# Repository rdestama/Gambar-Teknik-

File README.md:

# Gambar-Teknik-
D. R. N. Nuswantoro, "Gambar Teknik Semester 1 2021," File ini merupakan kumpulan tugas gambar teknik semester 1 tahun 2021 di UNY, Oct 2021.

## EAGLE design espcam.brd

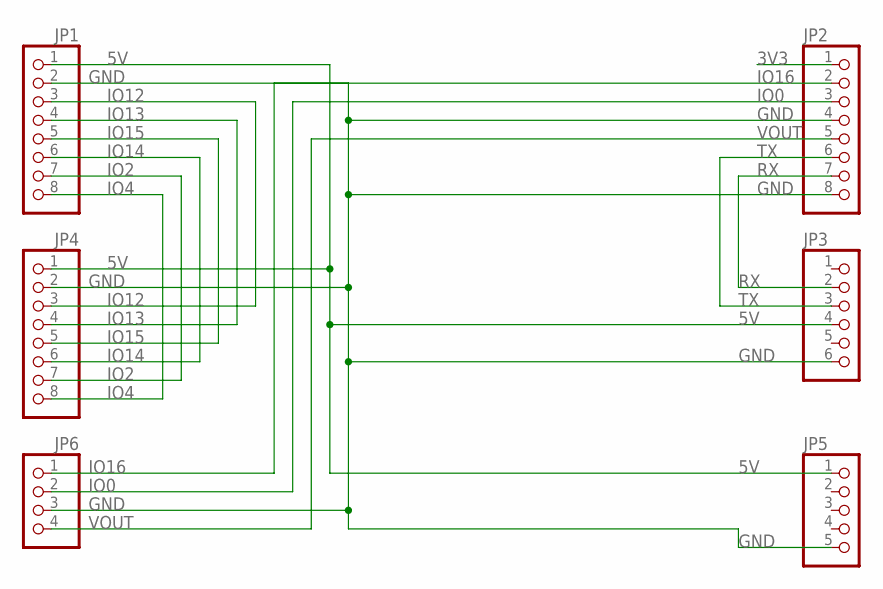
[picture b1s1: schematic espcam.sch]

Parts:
JP1, JP2, JP4: PINHD-1X8; 1X08
JP3: PINHD-1X6; 1X06
JP5: PINHD-1X5; 1X05
JP6: PINHD-1X4; 1X04

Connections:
3V3: JP2.1
5V: JP1.1, JP3.4, JP4.1, JP5.1
GND: JP1.2, JP2.4, JP2.8, JP3.6, JP4.2, JP5.5, JP6.3
IO0: JP2.3, JP6.2
IO2: JP1.7, JP4.7
IO4: JP1.8, JP4.8
IO12: JP1.3, JP4.3
IO13: JP1.4, JP4.4
IO14: JP1.6, JP4.6
IO15: JP1.5, JP4.5
IO16: JP2.2, JP6.1
RX: JP2.7, JP3.2
TX: JP2.6, JP3.3
VOUT: JP2.5, JP6.4

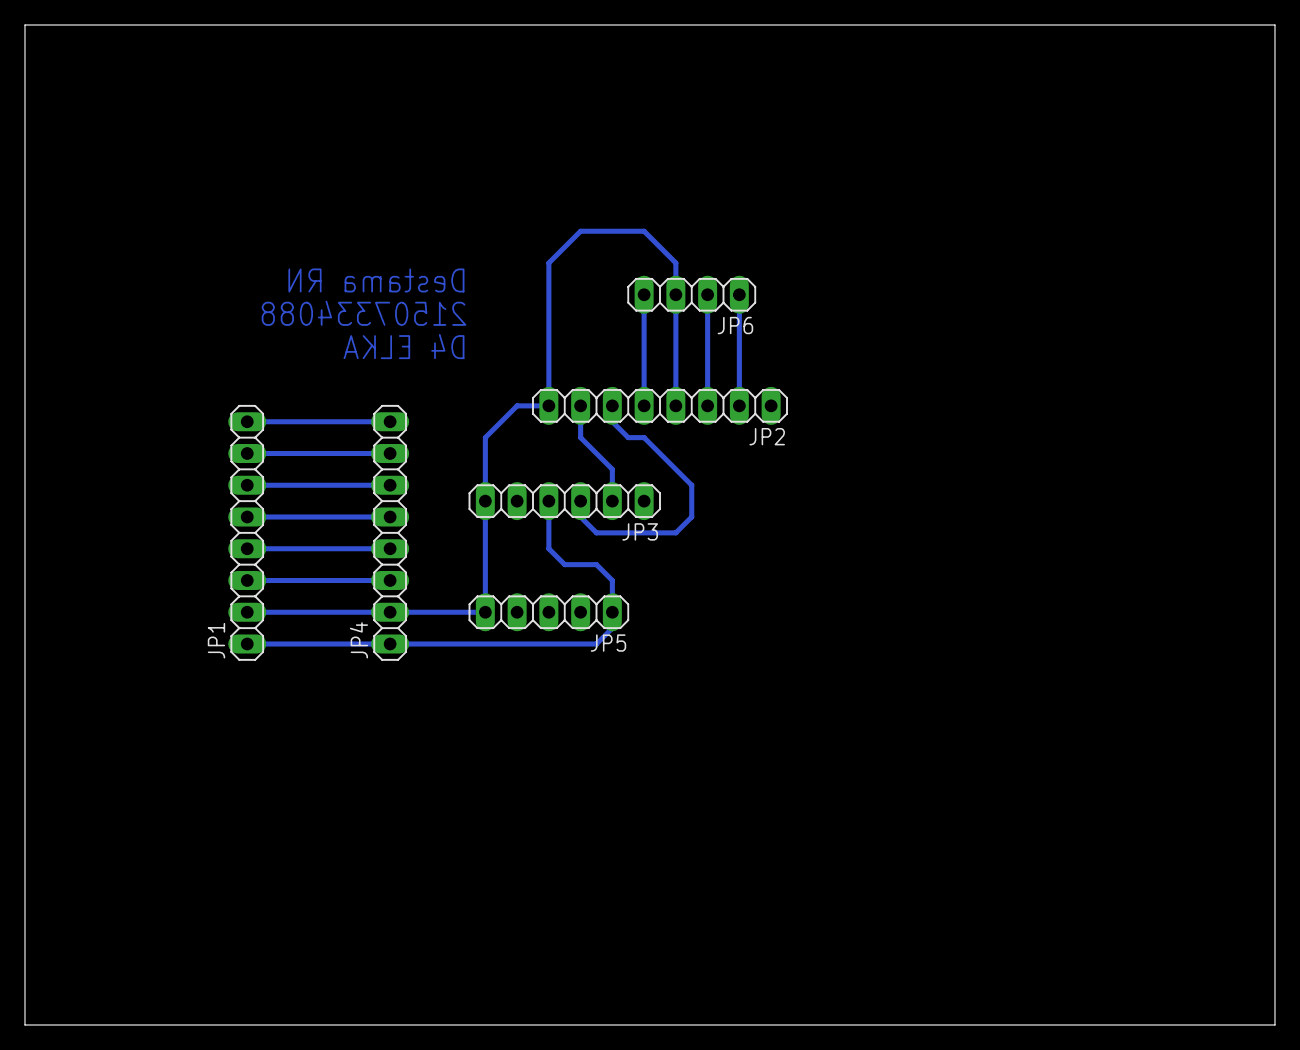
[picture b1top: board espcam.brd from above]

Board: 2 copper layers, 100.0 x 80.0 mm, 6 parts (0 on the bottom side), 13 nets.

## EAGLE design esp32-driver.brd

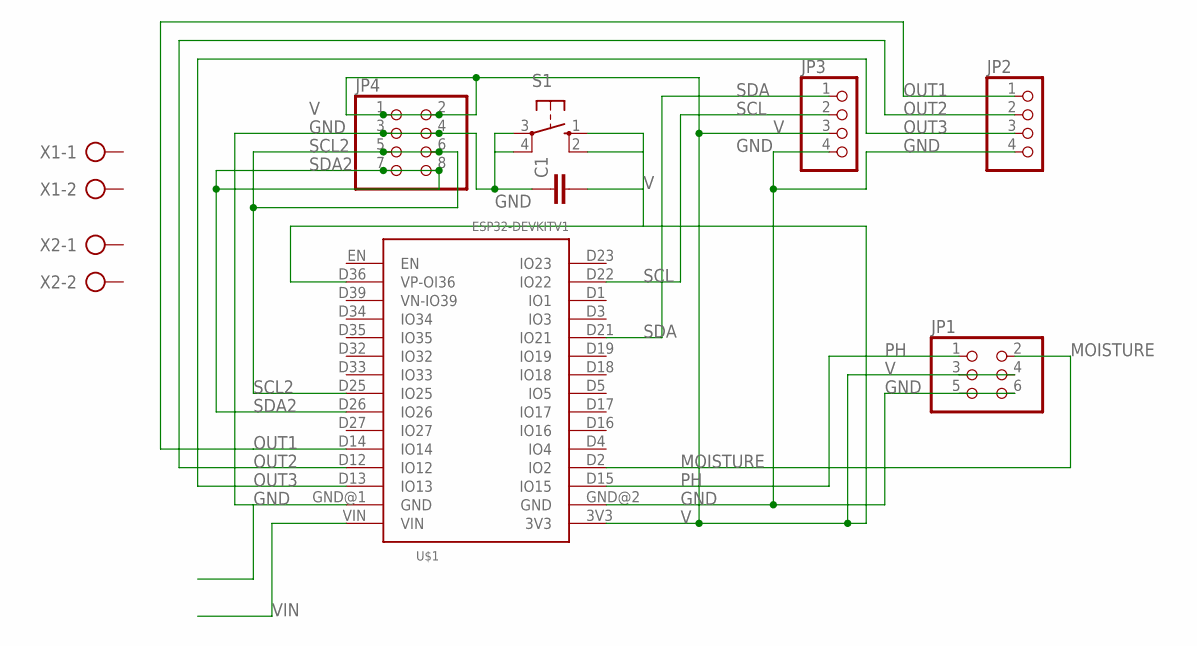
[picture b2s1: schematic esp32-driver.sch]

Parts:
C1: C-EU050-030X075; C050-030X075
JP1: PINHD-2X3; 2X03
JP2, JP3: PINHD-1X4; 1X04
JP4: PINHD-2X4; 2X04
S1: 10-XX; B3F-10XX
U$1: ESP32DEVKITV1; ESP32-DEVKITV1
X1, X2: AK300/2

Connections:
GND: C1.1, JP1.5, JP1.6, JP2.4, JP3.4, JP4.3, JP4.4, S1.3, S1.4 (P1), U$1.GND@1 (GND), U$1.GND@2 (GND)
MOISTURE: JP1.2, U$1.D2 (IO2)
OUT1: JP2.1, U$1.D14 (IO14)
OUT2: JP2.2, U$1.D12 (IO12)
OUT3: JP2.3, U$1.D13 (IO13)
PH: JP1.1, U$1.D15 (IO15)
SCL: JP3.2, U$1.D22 (IO22)
SCL2: JP4.5, JP4.6, U$1.D25 (IO25)
SDA: JP3.1, U$1.D21 (IO21)
SDA2: JP4.7, JP4.8, U$1.D26 (IO26)
V: C1.2, JP1.3, JP1.4, JP3.3, JP4.1, JP4.2, S1.1 (S), S1.2 (S1), U$1.3V3, U$1.D36 (VP-OI36)
VIN: U$1.VIN

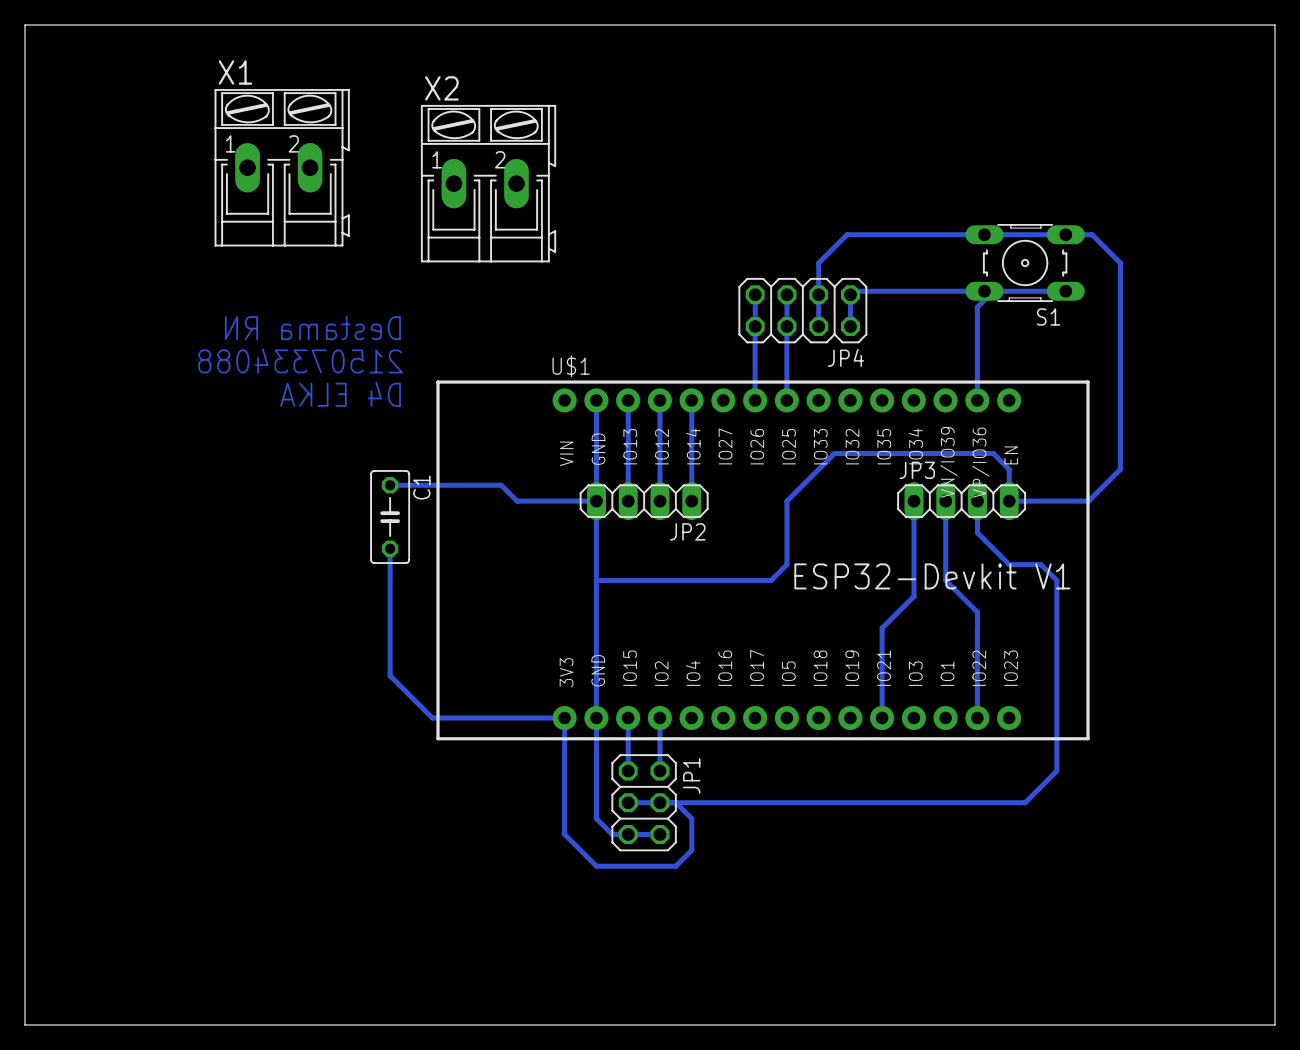
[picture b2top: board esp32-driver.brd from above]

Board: 2 copper layers, 100.0 x 80.0 mm, 9 parts (0 on the bottom side), 11 nets.

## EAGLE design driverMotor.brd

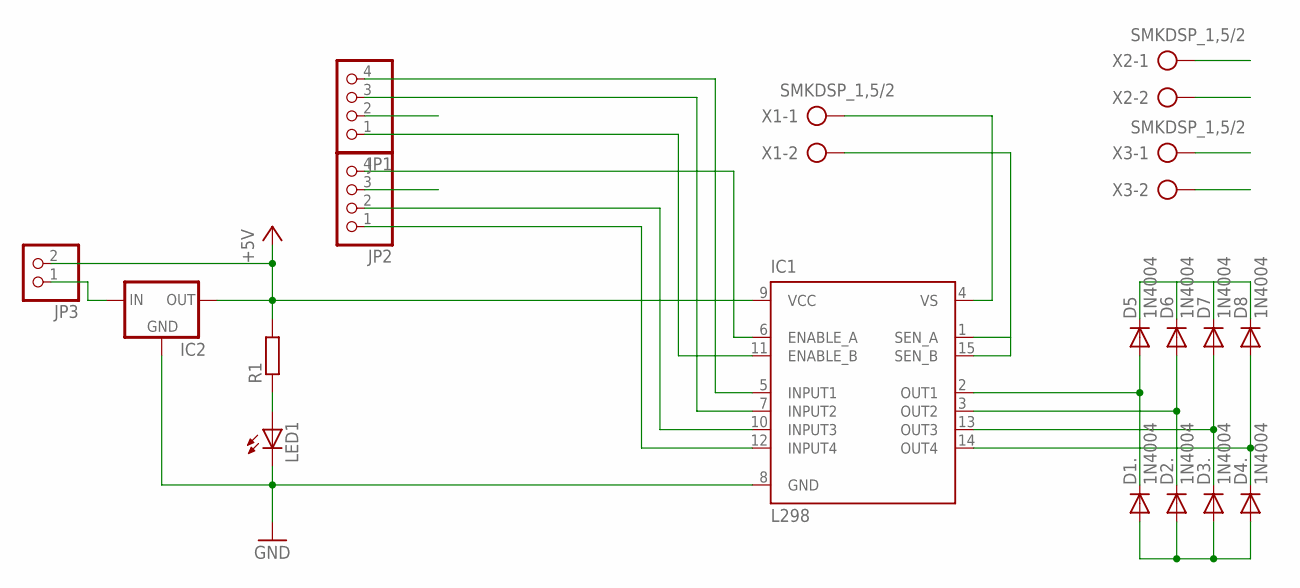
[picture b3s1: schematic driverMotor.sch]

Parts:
D1., D2., D3., D4., D5, D6, D7, D8: 1N4004; DO41-10
IC1: L298; MULTIWATT-15
IC2: 78MXXS
JP1, JP2: PINHD-1X4; 1X04
JP3: PINHD-1X2; 1X02
LED1: LED5MM
R1: R-EU_0411/12; 0411/12
X1, X2, X3: SMKDSP_1,5/2

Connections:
+5V: IC1.9 (VCC), IC2.OUT, JP1.2, JP3.2, R1.2
ENABLE_A: IC1.6 (ENABLE_A), JP2.4
ENABLE_B: IC1.11 (ENABLE_B), JP1.1
GND: D1..A, D2..A, D3..A, D4..A, IC1.1 (SEN_A), IC1.8 (GND), IC1.15 (SEN_B), IC2.GND, JP2.3, LED1.K (C), X1.2
INPUT1: IC1.5 (INPUT1), JP1.4
INPUT2: IC1.7 (INPUT2), JP1.3
INPUT3: IC1.10 (INPUT3), JP2.2
INPUT4: IC1.12 (INPUT4), JP2.1
LED: LED1.A, R1.1
MOTOR1_1: D1..C, D5.A, IC1.2 (OUT1), X2.1
MOTOR1_2: D2..C, D6.A, IC1.3 (OUT2), X2.2
MOTOR2_1: D3..C, D7.A, IC1.13 (OUT3), X3.1
MOTOR2_2: D4..C, D8.A, IC1.14 (OUT4), X3.2
unnamed: IC2.IN, JP3.1
VS: D5.C, D6.C, D7.C, D8.C, IC1.4 (VS), X1.1

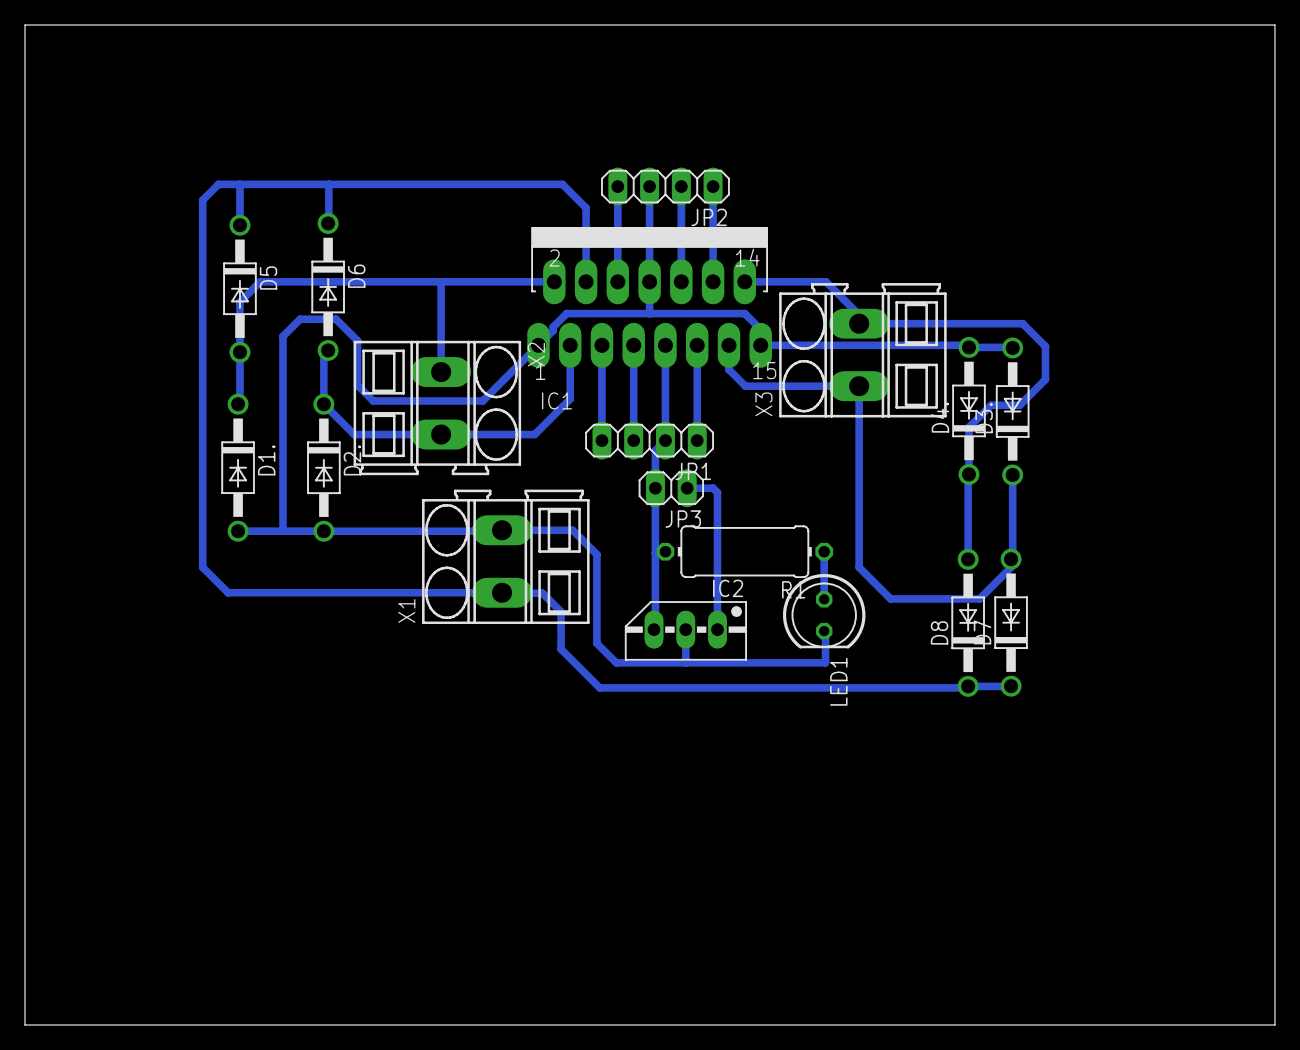
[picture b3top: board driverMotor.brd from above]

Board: 2 copper layers, 100.0 x 80.0 mm, 18 parts (0 on the bottom side), 15 nets.

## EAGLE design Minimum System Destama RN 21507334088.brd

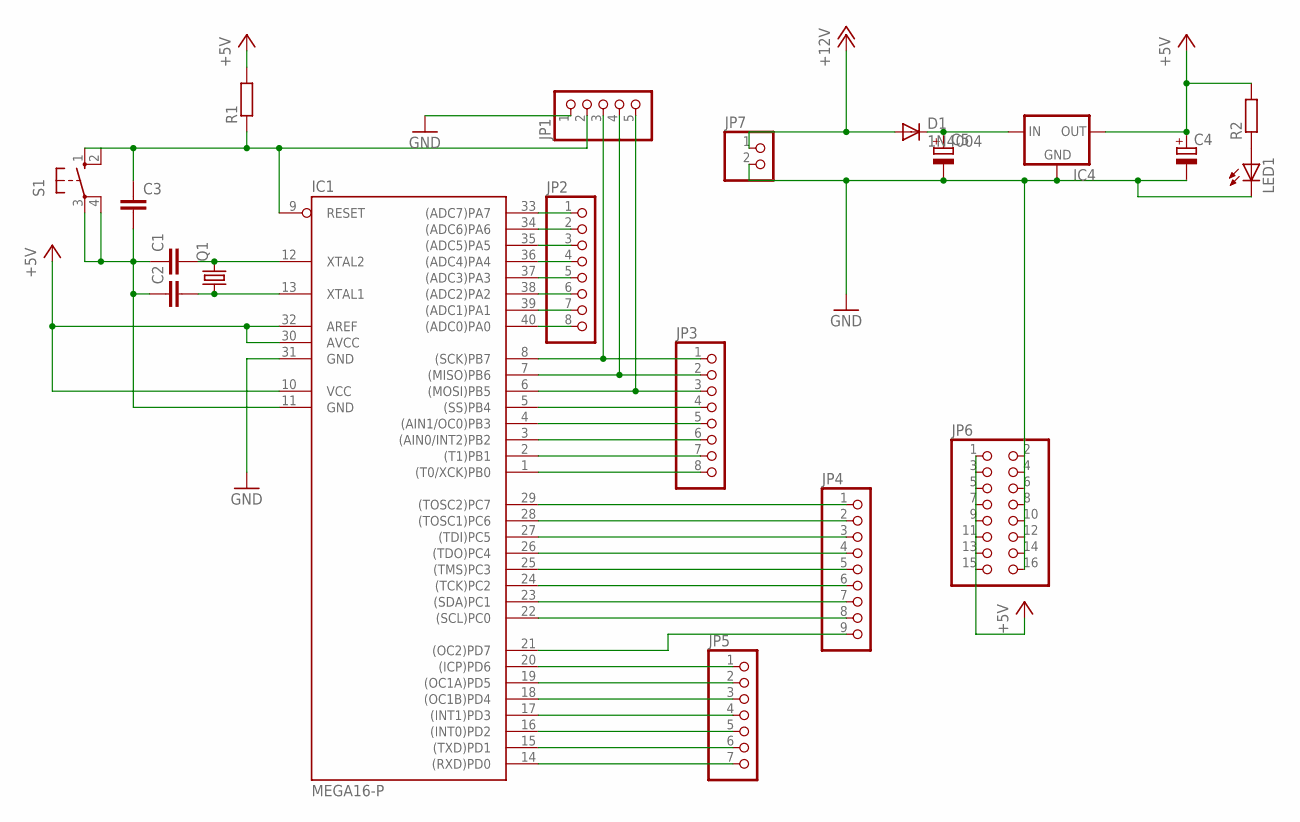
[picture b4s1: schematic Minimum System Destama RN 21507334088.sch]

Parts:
C1, C2: C-EU025-024X044; C025-024X044
C3: C-EU050-025X075; C050-025X075
C4, C5: CPOL-EUE2.5-5; E2,5-5
D1: 1N4004; DO41-10
IC1: MEGA16-P; DIL40
IC4: 78XXS
JP1: PINHD-1X5; 1X05
JP2, JP3: PINHD-1X8; 1X08
JP4: PINHD-1X9; 1X09
JP5: PINHD-1X7; 1X07
JP6: PINHD-2X8; 2X08
JP7: PINHD-1X2; 1X02
LED1: LED5MM
Q1: CRYSTALHC49U-V; HC49U-V
R1, R2: R-EU_0204/7; 0204/7
S1: 10-XX; B3F-10XX

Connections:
+5V: C4.+, IC1.10 (VCC), IC1.30 (AVCC), IC1.32 (AREF), IC4.OUT, JP6.1, JP6.3, JP6.5, JP6.7, JP6.9, JP6.11, JP6.13, JP6.15, R1.2, R2.2
+12V: D1.A, JP7.1
C0: IC1.22 ((SCL)PC0), JP4.8
C1: IC1.23 ((SDA)PC1), JP4.7
C2: IC1.24 ((TCK)PC2), JP4.6
C3: IC1.25 ((TMS)PC3), JP4.5
D7: IC1.14 ((RXD)PD0), JP5.7
GND: C1.1, C2.1, C3.2, C4.-, C5.-, IC1.11 (GND), IC1.31 (GND), IC4.GND, JP1.1, JP6.2, JP6.4, JP6.6, JP6.8, JP6.10, JP6.12, JP6.14, JP6.16, JP7.2, LED1.K (C), S1.3, S1.4 (P1)
unnamed: IC1.33 ((ADC7)PA7), JP2.1
unnamed: IC1.34 ((ADC6)PA6), JP2.2
unnamed: IC1.35 ((ADC5)PA5), JP2.3
unnamed: IC1.36 ((ADC4)PA4), JP2.4
unnamed: IC1.37 ((ADC3)PA3), JP2.5
unnamed: IC1.38 ((ADC2)PA2), JP2.6
unnamed: IC1.39 ((ADC1)PA1), JP2.7
unnamed: IC1.40 ((ADC0)PA0), JP2.8
unnamed: IC1.29 ((TOSC2)PC7), JP4.1
unnamed: IC1.28 ((TOSC1)PC6), JP4.2
unnamed: IC1.27 ((TDI)PC5), JP4.3
unnamed: IC1.5 ((SS)PB4), JP3.4
unnamed: IC1.20 ((ICP)PD6), JP5.1
unnamed: IC1.19 ((OC1A)PD5), JP5.2
unnamed: IC1.26 ((TDO)PC4), JP4.4
unnamed: IC1.6 ((MOSI)PB5), JP1.5, JP3.3
unnamed: IC1.4 ((AIN1/OC0)PB3), JP3.5
unnamed: IC1.3 ((AIN0/INT2)PB2), JP3.6
unnamed: IC1.2 ((T1)PB1), JP3.7
unnamed: IC1.1 ((T0/XCK)PB0), JP3.8
unnamed: C5.+, D1.C, IC4.IN
unnamed: IC1.15 ((TXD)PD1), JP5.6
unnamed: IC1.16 ((INT0)PD2), JP5.5
unnamed: IC1.17 ((INT1)PD3), JP5.4
unnamed: C3.1, IC1.9 (RESET), JP1.2, R1.1, S1.1 (S), S1.2 (S1)
unnamed: IC1.18 ((OC1B)PD4), JP5.3
unnamed: C1.2, IC1.12 (XTAL2), Q1.2
unnamed: C2.2, IC1.13 (XTAL1), Q1.1
unnamed: LED1.A, R2.1
unnamed: IC1.8 ((SCK)PB7), JP1.3, JP3.1
unnamed: IC1.7 ((MISO)PB6), JP1.4, JP3.2
RS: IC1.21 ((OC2)PD7), JP4.9

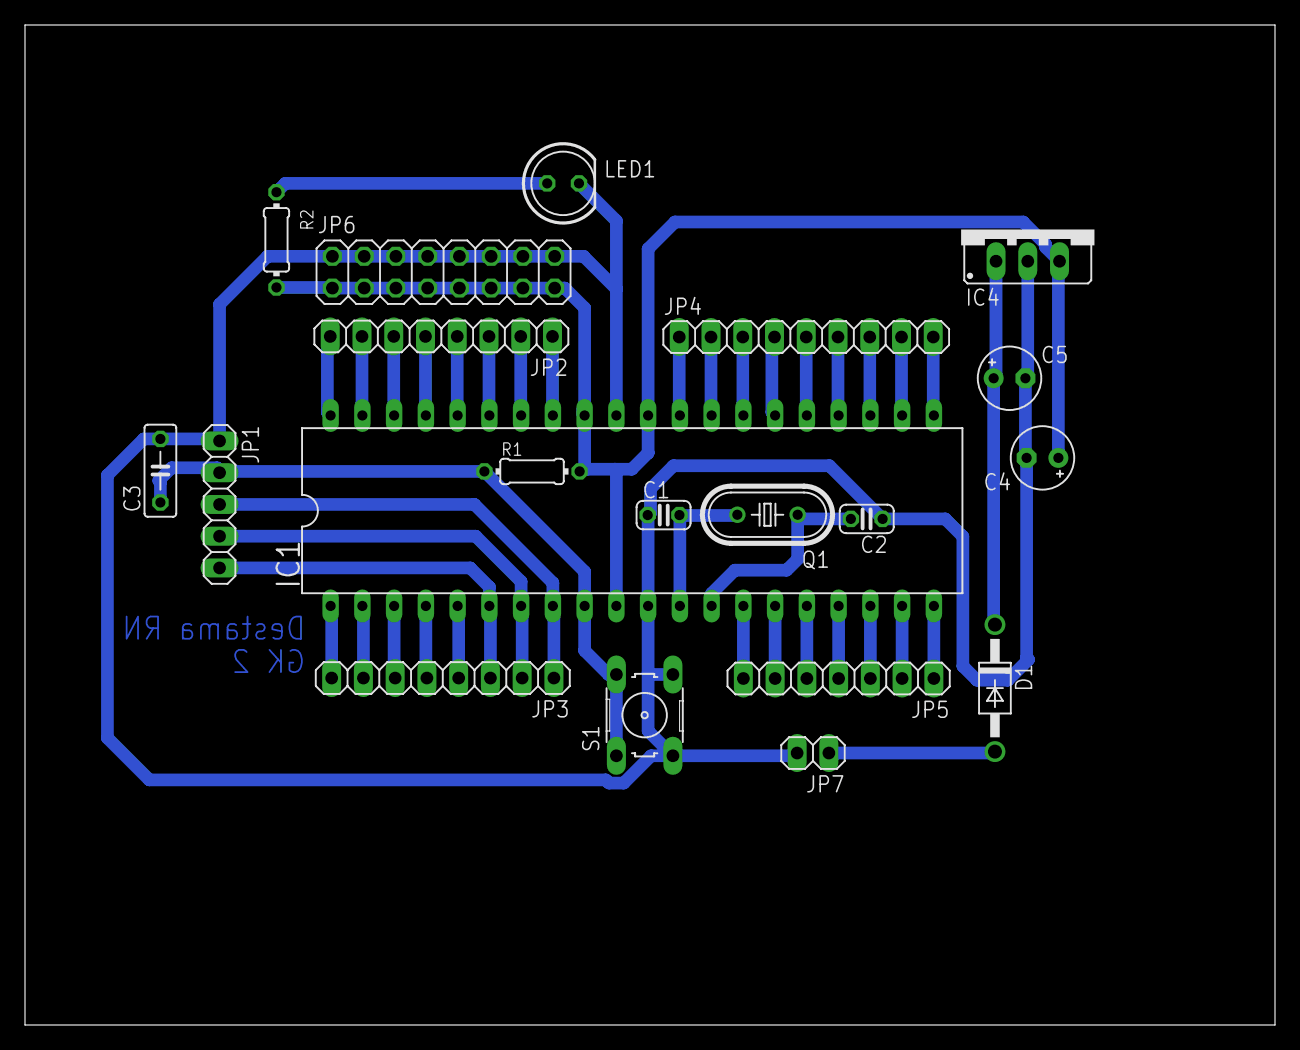
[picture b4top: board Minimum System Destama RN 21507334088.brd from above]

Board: 2 copper layers, 100.0 x 80.0 mm, 20 parts (0 on the bottom side), 40 nets.

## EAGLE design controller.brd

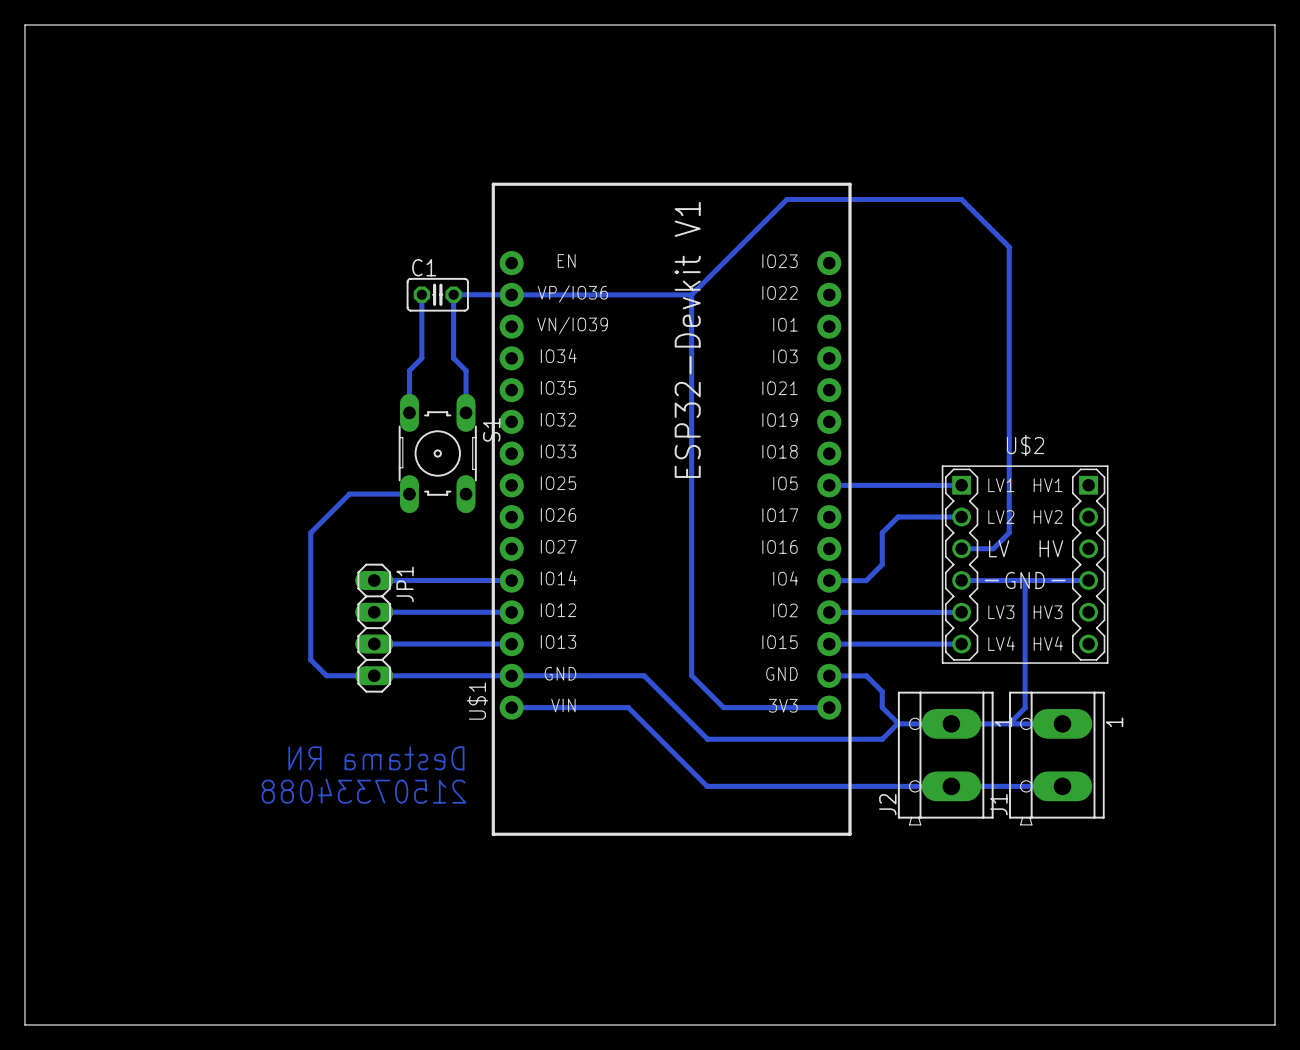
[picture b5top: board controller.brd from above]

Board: 2 copper layers, 100.0 x 80.0 mm, 7 parts (0 on the bottom side), 10 nets.

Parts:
C1: C025-025X050
J1, J2: CON_TERMINAL_BLOCK_02-5MM; TERMINAL_BLOCK_2P_5
JP1: 1X04
S1: B3F-10XX
U$1: ESP32DEVKITV1; ESP32-DEVKITV1
U$2: LEVEL-SHIFTER-4CH

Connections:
GND: C1.1, J1.1, J2.1, JP1.4, S1.3, S1.4, U$1.GND@1, U$1.GND@2, U$2.J1.4, U$2.J2.4
HV: J1.2, J2.2, U$1.VIN, U$2.J2.3
LV: C1.2, S1.1, S1.2, U$1.3V3, U$1.D36, U$2.J1.3
LV1: U$1.D5, U$2.J1.1
LV2: U$1.D4, U$2.J1.2
LV3: U$1.D2, U$2.J1.5
LV4: U$1.D15, U$2.J1.6
OUT1: JP1.1, U$1.D14
OUT2: JP1.2, U$1.D12
OUT3: JP1.3, U$1.D13

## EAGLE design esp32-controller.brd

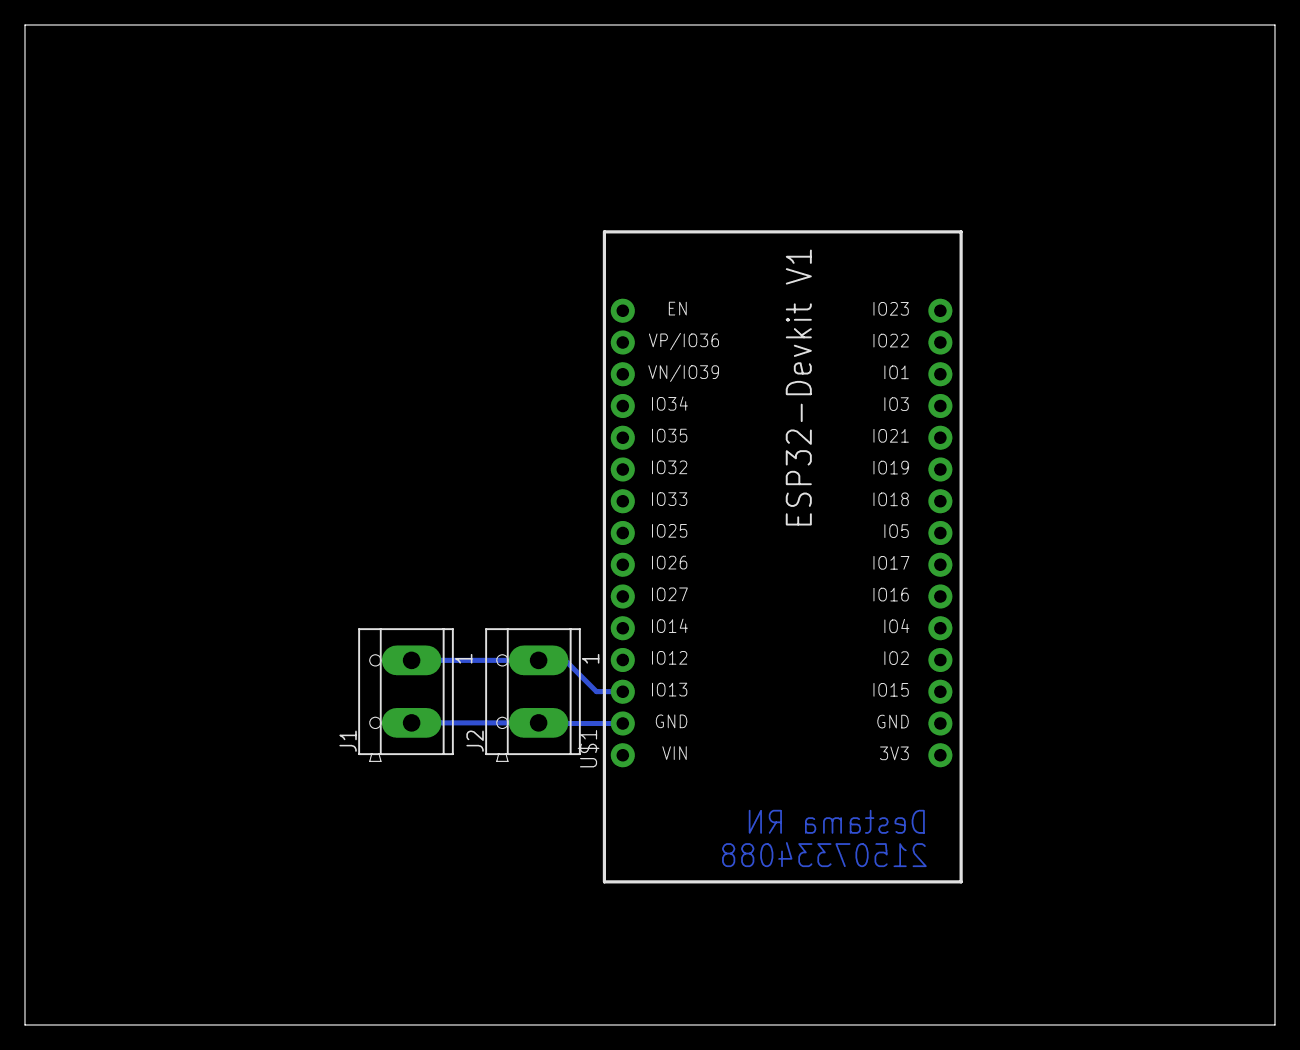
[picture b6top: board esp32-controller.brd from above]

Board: 2 copper layers, 100.0 x 80.0 mm, 3 parts (0 on the bottom side), 2 nets.

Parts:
J1, J2: CON_TERMINAL_BLOCK_02-5MM; TERMINAL_BLOCK_2P_5
U$1: ESP32DEVKITV1; ESP32-DEVKITV1

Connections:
GND: J1.1, J2.1, U$1.D13
HV: J1.2, J2.2, U$1.GND@1

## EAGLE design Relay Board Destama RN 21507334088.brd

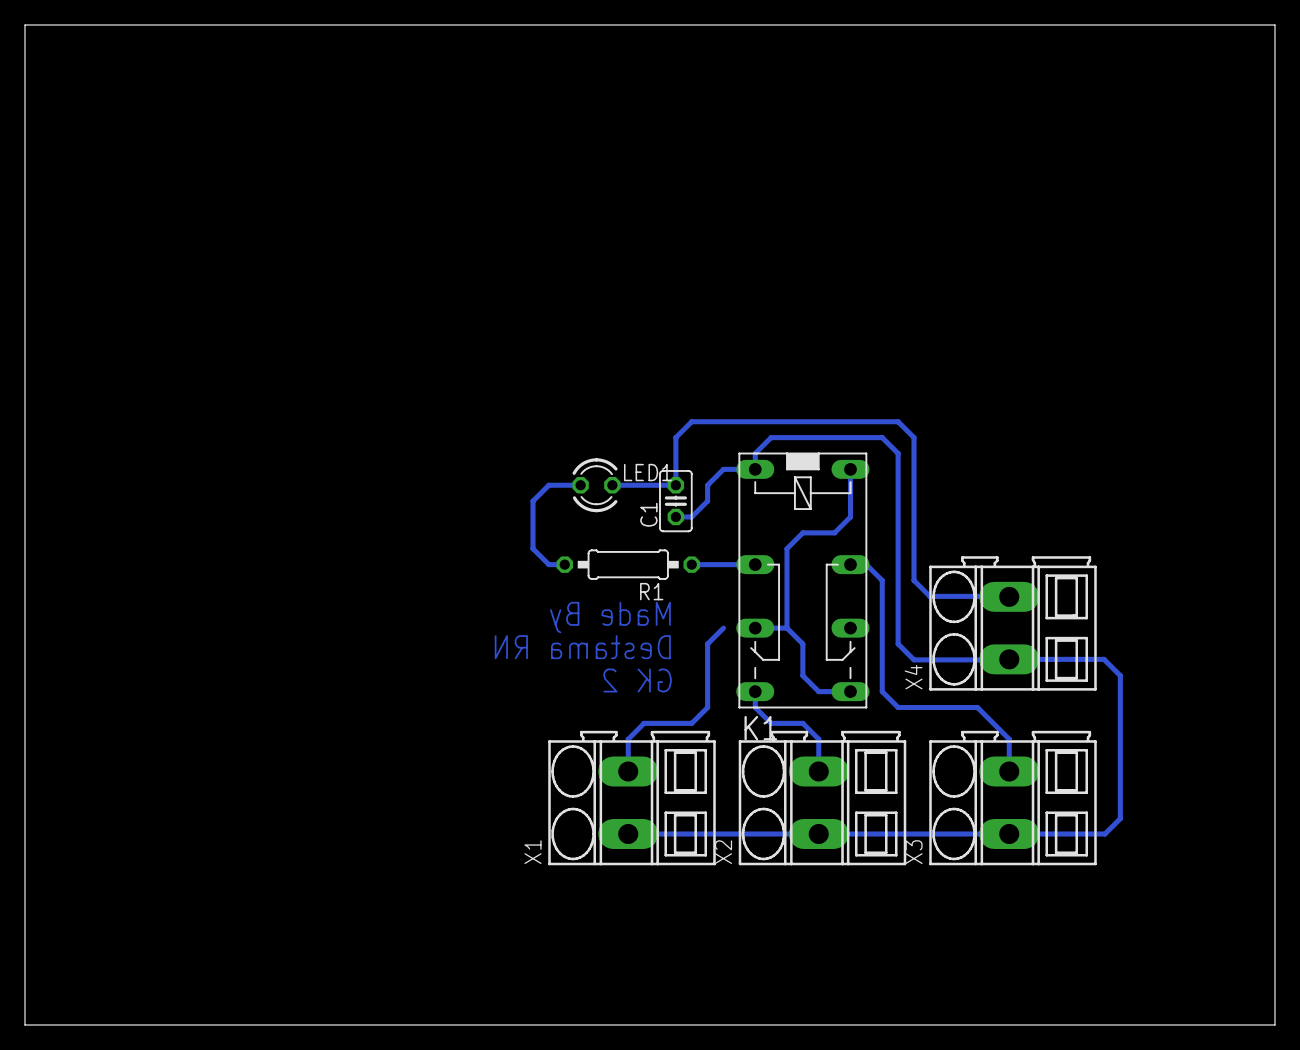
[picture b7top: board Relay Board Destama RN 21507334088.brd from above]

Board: 2 copper layers, 100.0 x 80.0 mm, 8 parts (0 on the bottom side), 7 nets.

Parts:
C1: C025-025X050
K1: 351
LED1: LED3MM
R1: 0207/10
X1, X2, X3, X4: SMKDSP_1,5/2

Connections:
GND: C1.1, K1.1, X1.1, X2.1, X3.1, X4.1
unnamed: K1.P1, R1.1
unnamed: LED1.A, R1.2
O1: K1.S1, X2.2
P2: K1.P2, X3.2
S12: K1.16, K1.O1, K1.S2, X1.2
VOUT: C1.2, LED1.K, X4.2

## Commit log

2021-09-20 Add files via upload
    Tugas Gambar Teknik (Low pass Filter Destama Rohman N (21507334088)
2021-09-22 Add files via upload
    Destana Rohman Nusawantoro (21507334088)
2021-10-27 Add files via upload
    Tugas Relay Board
2021-11-10 Add files via upload
    Tugas Gambar Teknik
2021-11-18 Add files via upload
    Membuat board drivermotor

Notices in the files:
parts and their libraries:
diy-model: Released under the Creative Commons Attribution 4.0 International License: http://creativecommons.org/licenses/by/4.0
